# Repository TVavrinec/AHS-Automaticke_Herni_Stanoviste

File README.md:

# AHS-Specifikace hrubý popis
Specifikace AHS (Automatické Herní Stanoviště), nástupcem Lucerny a BlackBoxu
Jde o statické zařízení sloužící jako herní stanoviště.
Mělo by tedy být mobilní jen natolik aby nebyl problém jej přepravovat.
Není ale cílem aby ho hráči nosil během hry nosil s sebou.

# Konkrétní uživatelské požadavky
- Dva LED kruhy jeden radiální a jeden axiální (tak jak na lucerně)
- Tlaková plocha (tak jak na lucerně ale doladit samotnou kontaktní plochu aby se zvýšila spolehlivost)
- Výdrž na baterii alespoň pět hodin aby bylo možné organizovat čtyřhodinovou hru s rezervou na nastavování atd.
- Elegantní zapínání (znamená ne powerbankou a kabelem!!!)
- Snadná montáž (znamená ne 16h na jeden kus)
- Servisně snadné připojený komunikační/GPS modul uvnitř zařízení (A9, MC60 ???)
- Servisně snadné připojená dvířka a jiné moduly vně základního zařízení
- Základní zvuková odezva (pískle, na pokročilejší zvuk bude modul)

# Základní struktura elektroniky

Elektronika je rozdělena na dvě desky, Led dsku a Hlavní desku.

## LedDeska

Oproti předchozím verzím je přidán LED-kruh i na druhou stranu LedDesky abychom se zbavili LED-pásku a odebrat výstupní konektor
- Přední axiální LEDkoví kruh z 60ti RGB LEDek
- Zadní radiální LEDkoví kruh z 60ti RGB LEDek (buď přímo radiální [buce cca třikrát dražší] nebo axiální s odraznou plochou [radializátorem])
- LDC1614 nebo LDC1314 + čtyři snímací cívky pro snímání tlakové plochy

## Hlavní deska 
- ESP32-S3
- Interní systémy
    - dohodnutí PD
    - bzučák (bez oscilátorové)
    - Power manager
        - jednočlánek
        - zapínání (ovládání na Mini UI)
        - step-up na 5V
        - LDO na 3V3
        - LDO na 1V8
        - nabíječka
        - hw ochrana podvybití
- Konektory na
    - ledDesku
    - komunikační modul
    - externí moduly
    - USB-C (nabíjení a primární programování [USB přímo z ESP, nebudeme zabírat místo převodníkem])
    - mini UI
    - kontakty na SemiSemafoří programátor
    - zbylé piny

## Mini UI
Minimalistické vývojové rozhraní.
- RESET tlačítka
- BOOT tlačítka
- zapínací tlačítko
- vypínací tlačítko bych spojil se zapínacím nebo možná s resetem (dlouhí stisk vypíná, nechci tam mít příliž mnoho tlačítek)
- dvě tlačítka 
- dvě obyčejné ledky?

# Popis jednotlivých bodů
## Interní systémy
### Dohodnutí PD
Vykomunykování vyššího napětí a proudu zajišťuje čip **AP33772** připojený na I2C ESP.

### Bzučák
Piezzo připojené mezi dva piny ESP aby bylo možné programově nastavit frekvenci a částečně i hlasitost.

### Power manager
#### Zapínání
Umožňuje uživateli zařízení zapnout tlačítkem.
Vypnutí je možné provést softwarově z ESP.

#### Step-up na 5V
Zajišťuje napájení světelným kruhům a externím modulům.
Maximální proud je sto ukrmit oba světelné kruhy a moduloví konektor.
*Je tedy sto dodat cca 7A*

#### LDO na 3V3
Z napětí 3.3V je napájeno ESP32S3, LCD1x14 a PD sink AP33772.
*Je tedy sto dodat cca 1A*

#### Nabíječka
Nabíjení probíhá přez USB-C, nabíječka je proto schopna rovzu z 5V.
Aby se ale zařízení dalo nabít rychleji je možno použít standard PowerDelivery s napětí až 21V.
Na nabíjení je proto použit chip **BQ24179YBGR**.

### Hw ochrana podvybití
Kvuli ochraně baterie se zařízení vypne pokud se baterie vybije pod 2.8V (podle https://web.archive.org/web/20101122230718/https://www.panasonic.com/industrial/includes/pdf/Panasonic_LiIon_Charging.pdf by napětí na článek nemělo klesnout pod 2.3V a AHS přidává rezervu 0.1V [ https://web.archive.org/web/20100413182032/http://www.panasonic.com/industrial/batteries-oem/oem/lithium-ion.aspx ]) 

## Konektory
### USB-C
D+ D- jsou napojeny přímo na ESP a CC piny jsou napojeny na AP33772(to přes I2C na ESP).

### Konektor komunikačního modulu
Na konektor, je z ESP vyvedeno: 
-   I2C
-   celý UART
-   FUL_CARD_POWER_OFF
-   RESET
-   WoWWAN (interrupt)

a mimo ESP je na konektoru:
-   napájení přímo z baterie
-   SIM

Pin-out M2 konektoru z https://files.waveshare.com/upload/0/02/SIM7600X-M2_Hardware_Design_V1.01.pdf

### Konektor na LedDesku

<-1--13-> 5V

<----14-> LED-DO

<-15-27-> GND

<----28-> 3V3

<----29-> LDC-GND

-----30-> LDC-INT

<----31-> SDA

<----32-- SCL

Pull-upy na I2C a na LDC-INT mají 4.7kΩ.
LDC-GND je na hlavní desce normální GND ale kvůli velkým proudum do ledek je v kabelu a na Led desce vedena odděleně.
Konektorem na 5V proteče alespoň 5A.

### Moduloví konektor

---> USART-RX

<--> 5V

<--> GND

<--- USART-TX

<--> GND

<--> 5V

---> INI

Všechny moduly jsou připojeny na jeden RX pin AHS.
Proto musí firmware AHS zajistit aby dva moduli nevysílali současně!
Každý modul má TX připojen přes rezistor 180Ω jako ochranu.

Interrupt na modulech se chová jako open-collector což je zajistit hardwarově.

AHS zajišťuje odolnost proti rušení na všech vstupních vodičích pomocí 4.7kΩ pull-up a odolnost proti zkratu na datových výstupních vodičích pomocí 180Ω.
Zároveň zajistí ESD ochranu všem vodičům co vedou z/do AHS.

Konektor je zároveň sto dodat napájení 5V s proudem v součty 2A.

Komunikace muže být vedena kabelem o délce až 25cm při komunikační rychlosti 5Mbps.
*Při dalším prodlužování linky bude třeba vodiče RX a TX vlnově přizpůsobit a doplnit linku terminátory*

## mechanická část
Základ AHS je mechanicky krátký válec s tlakovou plochou na horní ploše.
Kolem tlakové plochu je umístěn axiální světelný kruh a v horní části válcové plochy je radiální světelný kruh.

- Tělo minimálně v prototypu tisknuté
- Vyzkoušet různé provedení kontaktní plochy
    - Stejně jako na předchozí verzi FR4 ale tlustší aby se tolik nekroutila
    - PCB s hliníkovým jádrem + zalití do epoxidu nebo jiné dostatečně průsvitné hmoty
- Konektor externích modulu, USB-C a mini UI překrýt krytkou (ochrana před bordelem a náhodným mačkáním na tlačítka)

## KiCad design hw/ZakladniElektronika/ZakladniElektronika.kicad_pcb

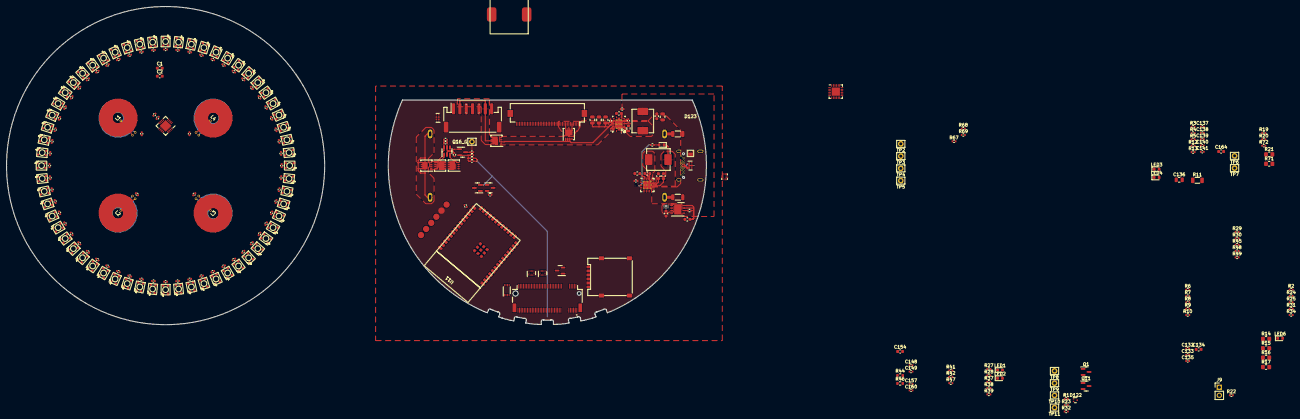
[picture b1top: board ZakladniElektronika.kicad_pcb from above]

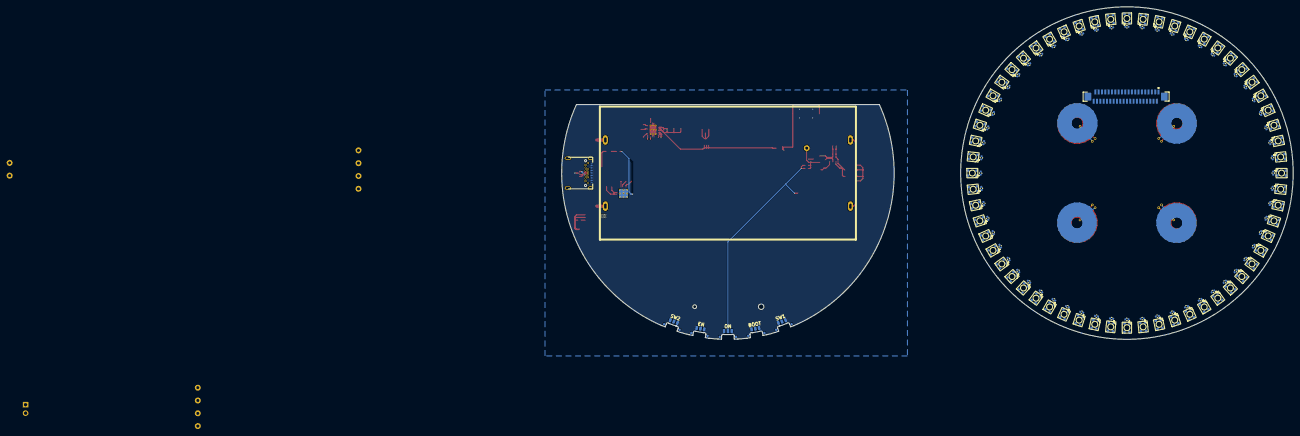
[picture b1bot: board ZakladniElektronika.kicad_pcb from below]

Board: 4 copper layers, 220.0 x 100.0 mm, 405 parts (128 on the bottom side), 258 nets.

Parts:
BZ1: Buzzer; PKLCS1212E-(RH-Logic_piezzo)
C1, C2, C6, C134, C145, C146, C147, C155: 10u; C_0603_1608Metric
C3, C132, C133, C138, C141, C142, C144, C148, C149, C163, C166: 1u; C_0402_1005Metric
C4, C7, C12, C13, C14, C15, C16, C17, C18, C19, C20, C21, C22, C23, C24, C25, C26, C27, C28, C29, C30, C31, C32, C33, C34, C35, C36, C37, C38, C39, C40, C41, C42, C43, C44, C45, C46, C47, C48, C49, C50, C51, C52, C53, C54, C55, C56, C57, C58, C59, C60, C61, C62, C63, C64, C65, C66, C67, C68, C69, C70, C71, C72, C73, C74, C75, C76, C77, C78, C79, C80, C81, C82, C83, C84, C85, C86, C87, C88, C89, C90, C91, C92, C93, C94, C95, C96, C97, C98, C99, C100, C101, C102, C103, C104, C105, C106, C107, C108, C109, C110, C111, C112, C113, C114, C115, C116, C117, C118, C119, C120, C121, C122, C123, C124, C125, C126, C127, C128, C129, C130, C131, C135, C137, C139, C140, C143, C151: 100n; C_0402_1005Metric
C5, C153, C156, C159: 22u; C_0805_2012Metric
C8, C9, C10, C11: 1000p; C_0402_1005Metric
C136: 10u; C_0805_2012Metric
C150, C154, C164: 4.7u; C_0603_1608Metric
C152, C165: 47n; C_0603_1608Metric
C157: 10n; C_0402_1005Metric
C160: 100p; C_0402_1005Metric
D1, D2, D3, D4, D5, D6, D7, D8, D9, D10, D11, D12, D13, D14, D15, D16, D17, D18, D19, D20, D21, D22, D23, D24, D25, D26, D27, D28, D29, D30, D31, D32, D33, D34, D35, D36, D37, D38, D39, D40, D41, D42, D43, D44, D45, D46, D47, D48, D49, D50, D51, D52, D53, D54, D55, D56, D57, D58, D59, D60, D61, D62, D63, D64, D65, D66, D67, D68, D69, D70, D71, D72, D73, D74, D75, D76, D77, D78, D79, D80, D81, D82, D83, D84, D85, D86, D87, D88, D89, D90, D91, D92, D93, D94, D95, D96, D97, D98, D99, D100, D101, D102, D103, D104, D105, D106, D107, D108, D109, D110, D111, D112, D113, D114, D115, D116, D117, D118, D119, D120: WS2812B; 3528RGBW-WS2812B
D122: D_Dual_CommonCathode_AAK_Parallel; SOT-723
D123: PTVSHC3N24; DFN3-2x2
F3, F4: 3A-6A; L_1206_3216Metric
J2: USB_C_Receptacle_USB2.0; USB31-TYPEC-33141-2FS
J3: Conn_2Rows-75Pins; Conn_M2
J4: Conn_01x07; JST_PH_S7B-PH-SM4-TB_1x07-1MP_P2.00mm_Horizontal
J7: ESP-Programing_conector
J9: Conn_01x02; PinHeader_1x02_P2.54mm_Vertical
J10: Conn_01x40; AFC11-S40ICC-00
J11: Conn_01x40; Hirose_FH12-40S-0.5SH_1x40-1MP_P0.50mm_Horizontal
L1, L2, L3, L4: L; PCB_coil
L6: 1.2u; L_Abracon_ASPI-0630LR
L7: 2.2u; L_Abracon_ASPI-0630LR
LED1, LED3, LED4, LED5, LED6: red; LED_0603_1608Metric
LED2: green; LED_0603_1608Metric
Q1, Q11, Q17: Q_NMOS_DGS-L; SOT-23
Q7: Q_PMOS_DGS-L; SOT-23
Q10, Q13: Q_PMOS_DGS-P; Diodes_PowerDI3333-8
Q12, Q14, Q15: Q_NMOS_DGS-P; Diodes_PowerDI3333-8
Qe: Q_NMOS_DGS-L; SOT-23
R1, R6, R7, R8, R9, R10, R12, R19, R20, R22, R23, R32, R34, R67, R70: 10k; R_0402_1005Metric
R2, R26, R41, R50, R60: 200k; R_0402_1005Metric
R3, R4: 5.1k; R_0402_1005Metric
R5, R13, R18, R24, R25, R31, R37, R38, R39, R45, R48: 4.7k; R_0402_1005Metric
R11: 10m; R_1206_3216Metric
R14, R16: 0-nc; R_0805_2012Metric_Pad1.20x1.40mm_HandSolder
R15, R17, R21, R71: 0; R_0805_2012Metric_Pad1.20x1.40mm_HandSolder
R27, R28: 1k; R_0402_1005Metric
R29, R30, R49, R69: 200; R_0402_1005Metric
R33: 2k; R_0402_1005Metric
R35: 470; R_0402_1005Metric
R36, R68: 1M; R_0402_1005Metric
R42: 3.92k; R_0402_1005Metric
R43, R44: 150k; R_0603_1608Metric
R46: 56k; R_0603_1608Metric
R47: 17.4k; R_0402_1005Metric
R72: 100; R_0402_1005Metric
SW1, SW2: SW_Push; TCF2QR
SW3: ON; TCF2QR
SW4: BOOT; TCF2QR
SW5: EN; TCF2QR
TP1: Q16_G; Pin_D0.9mm_L10.0mm_W2.4mm_FlatFork
TP2: TestPoint-BAT; Pin_D0.9mm_L10.0mm_W2.4mm_FlatFork
TP3: TestPoint-VCC; Pin_D0.9mm_L10.0mm_W2.4mm_FlatFork
TP4: TestPoint-BUTTON_ON; Pin_D0.9mm_L10.0mm_W2.4mm_FlatFork
TP5: TestPoint-EN_ALL; Pin_D0.9mm_L10.0mm_W2.4mm_FlatFork
TP6: TestPoint-Charger_QON; Pin_D0.9mm_L10.0mm_W2.4mm_FlatFork
TP7: TestPoint-Charger_ILIM; Pin_D0.9mm_L10.0mm_W2.4mm_FlatFork
TP8: TestPoint-5V_EN; Pin_D0.9mm_L10.0mm_W2.4mm_FlatFork
TP9: TestPoint-5V; Pin_D0.9mm_L10.0mm_W2.4mm_FlatFork
TP10: TestPoint-5V_B; Pin_D0.9mm_L10.0mm_W2.4mm_FlatFork
TP11: TestPoint-5V_A; Pin_D0.9mm_L10.0mm_W2.4mm_FlatFork
U1: LDC1614; WQFN-16-1EP_4x4mm_P0.5mm_EP2.6x2.6mm
U2, U6: TXB0304RUT; Texas_R-PUQFN-N12
U3: TPS61088RHLR; RHL0020A
U4: AP33772; QFN-24-1EP_4x4mm_P0.5mm_EP2.6x2.6mm
U5, U13: TPD4E02B04DQA; USON-10_2.5x1.0mm_P0.5mm
U7: SL8261D-G3JE; SOT-23-6
U8: PCA9306DC; VSSOP-8_2.3x2mm_P0.5mm
U9: BQ25895RTW; Texas_S-PWQFN-N24_EP2.7x2.7mm_ThermalVias
U11: ESP32-S3-WROOM
U12: LD39200; DFN-8-1EP_4x4mm_P0.8mm_EP2.3x3.24mm
U15: TS3USB3031; Texas_X2QFN-12_1.6x1.6mm_P0.4mm
U17: BateriCell_2x; battery_dock
U52: MCP1700x-180xxTT; SOT-23
U53: SMN-305-ARP7

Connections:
/HlavniDeska/3V3: C134.2, C135.2, C149.1, C155.1, J7.1 (VCC), J9.2, J11.36, LED6.2 (A), R2.1, R9.1, R10.1, R23.1, R34.1, R37.1, R38.1, R39.1, R45.2, R48.2, R67.2, R70.2, U2.11 (VCCB), U6.11 (VCCB), U11.2 (3V3), U12.1 (OUT), U12.2 (OUT), U12.3 (ADJ/SENSE), U15.12 (VCC), U52.3 (VI)
/HlavniDeska/5V-OUT: J11.1, J11.2, J11.3, J11.4, J11.5, J11.6, J11.7, J11.8, J11.9, J11.10, J11.11, J11.12, J11.13, Q13.5 (D), TP10.1
/HlavniDeska/C.D+: J2.A6 (D+), J2.B6 (D+), U13.5 (IO4), U15.11 (D+)
/HlavniDeska/C.D-: J2.A7 (D-), J2.B7 (D-), U13.4 (IO3), U15.10 (D-)
/HlavniDeska/ESP32S3/BOOT: C132.1, J7.4 (BOOT), R9.2, SW4.2, U11.27 (IO00-PU)
/HlavniDeska/ESP32S3/EN: C133.1, J7.3 (EN), R10.2, SW5.2, U11.3 (EN)
/HlavniDeska/ESP32S3/IO01: BZ1.2 (+), U11.39 (IO01)
/HlavniDeska/ESP32S3/IO02: R49.2, U5.4 (IO3), U11.38 (IO02)
/HlavniDeska/ESP32S3/IO03-PD: BZ1.1 (-), R8.1, U11.15 (IO03-PD)
/HlavniDeska/ESP32S3/IO07: U6.10 (B1), U11.7 (IO07)
/HlavniDeska/ESP32S3/IO08: J3.6, U11.12 (IO08)
/HlavniDeska/ESP32S3/IO15: J3.1, U11.8 (IO15)
/HlavniDeska/ESP32S3/IO16: J3.75, U11.9 (IO16)
/HlavniDeska/ESP32S3/IO17: J3.69, U11.10 (IO17)
/HlavniDeska/ESP32S3/IO18: J3.21, U11.11 (IO18)
/HlavniDeska/ESP32S3/IO21: R69.2, U11.23 (IO21)
/HlavniDeska/ESP32S3/IO35: Qe.1 (D), R70.1, U11.28 (IO35)
/HlavniDeska/ESP32S3/IO36: SW1.2, U11.29 (IO36)
/HlavniDeska/ESP32S3/IO37: SW2.2, U11.30 (IO37)
/HlavniDeska/ESP32S3/IO38: LED1.2 (A), U11.31 (IO38)
/HlavniDeska/ESP32S3/IO39: LED2.2 (A), U11.32 (IO39)
/HlavniDeska/ESP32S3/IO41: R29.2, U5.1 (IO1), U11.34 (IO41)
/HlavniDeska/ESP32S3/IO42: R30.2, U5.2 (IO2), U11.35 (IO42)
/HlavniDeska/ESP32S3/IO45-PD: D122.1 (K), Q11.2 (G), R7.1, U11.26 (IO45-PD)
/HlavniDeska/ESP32S3/IO46-PD: D122.2 (K), Q1.2 (G), R6.1, U11.16 (IO46-PD)
/HlavniDeska/ESP32S3/RX_ESP: J7.5 (RX), U11.36 (IO44-RX)
/HlavniDeska/ESP32S3/TX_ESP: J7.6 (TX), U11.37 (IO43-TX)
/HlavniDeska/ESP.D+: U11.14 (IO20-D+), U15.5 (USB2+)
/HlavniDeska/ESP.D-: U11.13 (IO19-D-), U15.6 (USB2-)
/HlavniDeska/GPSKomunikacniModul/1V8: C148.1, R24.1, R25.1, U2.1 (VCCA), U2.12 (OE), U6.1 (VCCA), U6.12 (OE), U8.2 (VREF1), U52.2 (VO)
/HlavniDeska/GPSKomunikacniModul/SCL(1.8V): J3.40, R24.2, U8.3 (SCL1)
/HlavniDeska/GPSKomunikacniModul/SDA(1.8V): J3.42, R25.2, U8.4 (SDA1)
/HlavniDeska/GPSKomunikacniModul/SIM_CD: J3.66, U53.D (CD)
/HlavniDeska/GPSKomunikacniModul/SIM_CLK: J3.32, U53.3 (CLK)
/HlavniDeska/GPSKomunikacniModul/SIM_I/O: J3.34, U53.7 (I/O)
/HlavniDeska/GPSKomunikacniModul/SIM_RST: J3.30, U53.2 (RST)
/HlavniDeska/GPSKomunikacniModul/SIM_VCC: J3.36, U53.1 (VCC)
/HlavniDeska/GPSKomunikacniModul/UART_CTS(O)(1.8V): J3.56, U2.4 (A3)
/HlavniDeska/GPSKomunikacniModul/UART_DTR(I)(1.8V): J3.52, U6.3 (A2)
/HlavniDeska/GPSKomunikacniModul/UART_RTS(I)(1.8V): J3.54, U2.5 (A4)
/HlavniDeska/GPSKomunikacniModul/UART_RXD(I)(1.8V): R14.1, R15.1, U2.3 (A2)
/HlavniDeska/GPSKomunikacniModul/UART_TXD(O)(1.8V): R16.1, R17.1, U2.2 (A1)
/HlavniDeska/INT: J3.23, J11.38, R34.2, R38.2, U4.9 (GPIO3), U9.7 (INT), U11.4 (IO04)
/HlavniDeska/IO40: J11.27, U11.33 (IO40)
/HlavniDeska/KM_CST: U2.8 (B3), U11.19 (IO11)
/HlavniDeska/KM_DTR: U6.9 (B2), U11.17 (IO09)
/HlavniDeska/KM_RTS: U2.7 (B4), U11.18 (IO10)
/HlavniDeska/KM_RXD: U2.9 (B2), U11.20 (IO12)
/HlavniDeska/KM_TXD: U2.10 (B1), U11.21 (IO13)
/HlavniDeska/KomunikacniModul.D+: J3.9, U15.7 (MHL+)
/HlavniDeska/KomunikacniModul.D-: J3.7, U15.8 (MHL-)
/HlavniDeska/ModulovyKonektor/5V: J4.2, J4.6, Q10.5 (D), TP11.1, U5.5 (IO4)
/HlavniDeska/Nabijecka.D+: U9.2 (D+), U15.3 (USB1+)
/HlavniDeska/Nabijecka.D-: U9.3 (D-), U15.4 (USB1-)
/HlavniDeska/SCL: J11.40, R37.2, U4.5 (SCL), U8.6 (SCL2), U9.5 (SCL), U11.5 (IO05)
/HlavniDeska/SDA: J11.39, R39.2, U4.4 (SDA), U8.5 (SDA2), U9.6 (SDA), U11.6 (IO06)
/HlavniDeska/SpravceNapajeni/5V-IN: C142.1, C153.1, C156.1, C159.1, Q10.1 (S), Q10.2 (S), Q10.3 (S), Q13.1 (S), Q13.2 (S), Q13.3 (S), R1.1, R32.1, R46.1, TP9.1, U3.14 (VOUT), U3.15 (VOUT), U3.16 (VOUT)
/HlavniDeska/SpravceNapajeni/DSEL: R23.2, U9.24 (DSEL), U15.1 (SEL0)
/HlavniDeska/SpravceNapajeni/Nabijecka/STAT: R18.1, U9.4 (STAT)
/HlavniDeska/SpravceNapajeni/NapajeciRozcesti/EN-5V: D122.3 (A), R41.2, TP8.1, U3.2 (EN)
/HlavniDeska/SpravceNapajeni/VBUS: C137.2, C141.1, C166.1, R11.2, U4.22 (VUSB), U4.24 (VCC), U9.1 (VBUS)
/HlavniDeska/USB/AP-3V3: C139.2, U4.12 (3V3)
/HlavniDeska/USB/USB_CC1: J2.A5 (CC1), R4.1, U4.17 (CC1), U13.1 (IO1)
/HlavniDeska/USB/USB_CC2: J2.B5 (CC2), R3.1, U4.16 (CC2), U13.2 (IO2)
/HlavniDeska/USB/V_USB: C136.1, C137.1, D123.3 (K), J2.A4 (VBUS), J2.A9 (VBUS), J2.B4 (VBUS), J2.B9 (VBUS), LED3.2 (A), R11.1, U4.1 (ISENP)
/LedDeska/3V3: C3.1, C4.1, J10.36, U1.7 (VDD)
/LedDeska/5V: C1.1, C2.1, C12.1, C13.1, C14.1, C15.1, C16.1, C17.1, C18.1, C19.1, C20.1, C21.1, C22.1, C23.1, C24.1, C25.1, C26.1, C27.1, C28.1, C29.1, C30.1, C31.1, C32.1, C33.1, C34.1, C35.1, C36.1, C37.1, C38.1, C39.1, C40.1, C41.1, C42.1, C43.1, C44.1, C45.1, C46.1, C47.1, C48.1, C49.1, C50.1, C51.1, C52.1, C53.1, C54.1, C55.1, C56.1, C57.1, C58.1, C59.1, C60.1, C61.1, C62.1, C63.1, C64.1, C65.1, C66.1, C67.1, C68.1, C69.1, C70.1, C71.1, C72.1, C73.1, C74.1, C75.1, C76.1, C77.1, C78.1, C79.1, C80.1, C81.1, C82.1, C83.1, C84.1, C85.1, C86.1, C87.1, C88.1, C89.1, C90.1, C91.1, C92.1, C93.1, C94.1, C95.1, C96.1, C97.1, C98.1, C99.1, C100.1, C101.1, C102.1, C103.1, C104.1, C105.1, C106.1, C107.1, C108.1, C109.1, C110.1, C111.1, C112.1, C113.1, C114.1, C115.1, C116.1, C117.1, C118.1, C119.1, C120.1, C121.1, C122.1, C123.1, C124.1, C125.1, C126.1, C127.1, C128.1, C129.1, C130.1, C131.1, D1.1 (VDD), D2.1 (VDD), D3.1 (VDD), D4.1 (VDD), D5.1 (VDD), D6.1 (VDD), D7.1 (VDD), D8.1 (VDD), D9.1 (VDD), D10.1 (VDD), D11.1 (VDD), D12.1 (VDD), D13.1 (VDD), D14.1 (VDD), D15.1 (VDD), D16.1 (VDD), D17.1 (VDD), D18.1 (VDD), D19.1 (VDD), D20.1 (VDD), D21.1 (VDD), D22.1 (VDD), D23.1 (VDD), D24.1 (VDD), D25.1 (VDD), D26.1 (VDD), D27.1 (VDD), D28.1 (VDD), D29.1 (VDD), D30.1 (VDD), D31.1 (VDD), D32.1 (VDD), D33.1 (VDD), D34.1 (VDD), D35.1 (VDD), D36.1 (VDD), D37.1 (VDD), D38.1 (VDD), D39.1 (VDD), D40.1 (VDD), D41.1 (VDD), D42.1 (VDD), D43.1 (VDD), D44.1 (VDD), D45.1 (VDD), D46.1 (VDD), D47.1 (VDD), D48.1 (VDD), D49.1 (VDD), D50.1 (VDD), D51.1 (VDD), D52.1 (VDD), D53.1 (VDD), D54.1 (VDD), D55.1 (VDD), D56.1 (VDD), D57.1 (VDD), D58.1 (VDD), D59.1 (VDD), D60.1 (VDD), D61.1 (VDD), D62.1 (VDD), D63.1 (VDD), D64.1 (VDD), D65.1 (VDD), D66.1 (VDD), D67.1 (VDD), D68.1 (VDD), D69.1 (VDD), D70.1 (VDD), D71.1 (VDD), D72.1 (VDD), D73.1 (VDD), D74.1 (VDD), D75.1 (VDD), D76.1 (VDD), D77.1 (VDD), D78.1 (VDD), D79.1 (VDD), D80.1 (VDD), D81.1 (VDD), D82.1 (VDD), D83.1 (VDD), D84.1 (VDD), D85.1 (VDD), D86.1 (VDD), D87.1 (VDD), D88.1 (VDD), D89.1 (VDD), D90.1 (VDD), D91.1 (VDD), D92.1 (VDD), D93.1 (VDD), D94.1 (VDD), D95.1 (VDD), D96.1 (VDD), D97.1 (VDD), D98.1 (VDD), D99.1 (VDD), D100.1 (VDD), D101.1 (VDD), D102.1 (VDD), D103.1 (VDD), D104.1 (VDD), D105.1 (VDD), D106.1 (VDD), D107.1 (VDD), D108.1 (VDD), D109.1 (VDD), D110.1 (VDD), D111.1 (VDD), D112.1 (VDD), D113.1 (VDD), D114.1 (VDD), D115.1 (VDD), D116.1 (VDD), D117.1 (VDD), D118.1 (VDD), D119.1 (VDD), D120.1 (VDD), J10.1, J10.2, J10.3, J10.4, J10.5, J10.6, J10.7, J10.8, J10.9, J10.10, J10.11, J10.12, J10.13
/LedDeska/AN-GND: C3.2, C4.2, J10.37, U1.3 (CLKIN), U1.4 (ADDR), U1.6 (SD), U1.8 (GND), U1.17 (GND)
/LedDeska/INT-LDC: J10.38, U1.5 (INTB)
/LedDeska/LED-GND: C1.2, C2.2, C12.2, C13.2, C14.2, C15.2, C16.2, C17.2, C18.2, C19.2, C20.2, C21.2, C22.2, C23.2, C24.2, C25.2, C26.2, C27.2, C28.2, C29.2, C30.2, C31.2, C32.2, C33.2, C34.2, C35.2, C36.2, C37.2, C38.2, C39.2, C40.2, C41.2, C42.2, C43.2, C44.2, C45.2, C46.2, C47.2, C48.2, C49.2, C50.2, C51.2, C52.2, C53.2, C54.2, C55.2, C56.2, C57.2, C58.2, C59.2, C60.2, C61.2, C62.2, C63.2, C64.2, C65.2, C66.2, C67.2, C68.2, C69.2, C70.2, C71.2, C72.2, C73.2, C74.2, C75.2, C76.2, C77.2, C78.2, C79.2, C80.2, C81.2, C82.2, C83.2, C84.2, C85.2, C86.2, C87.2, C88.2, C89.2, C90.2, C91.2, C92.2, C93.2, C94.2, C95.2, C96.2, C97.2, C98.2, C99.2, C100.2, C101.2, C102.2, C103.2, C104.2, C105.2, C106.2, C107.2, C108.2, C109.2, C110.2, C111.2, C112.2, C113.2, C114.2, C115.2, C116.2, C117.2, C118.2, C119.2, C120.2, C121.2, C122.2, C123.2, C124.2, C125.2, C126.2, C127.2, C128.2, C129.2, C130.2, C131.2, D1.3 (VSS), D2.3 (VSS), D3.3 (VSS), D4.3 (VSS), D5.3 (VSS), D6.3 (VSS), D7.3 (VSS), D8.3 (VSS), D9.3 (VSS), D10.3 (VSS), D11.3 (VSS), D12.3 (VSS), D13.3 (VSS), D14.3 (VSS), D15.3 (VSS), D16.3 (VSS), D17.3 (VSS), D18.3 (VSS), D19.3 (VSS), D20.3 (VSS), D21.3 (VSS), D22.3 (VSS), D23.3 (VSS), D24.3 (VSS), D25.3 (VSS), D26.3 (VSS), D27.3 (VSS), D28.3 (VSS), D29.3 (VSS), D30.3 (VSS), D31.3 (VSS), D32.3 (VSS), D33.3 (VSS), D34.3 (VSS), D35.3 (VSS), D36.3 (VSS), D37.3 (VSS), D38.3 (VSS), D39.3 (VSS), D40.3 (VSS), D41.3 (VSS), D42.3 (VSS), D43.3 (VSS), D44.3 (VSS), D45.3 (VSS), D46.3 (VSS), D47.3 (VSS), D48.3 (VSS), D49.3 (VSS), D50.3 (VSS), D51.3 (VSS), D52.3 (VSS), D53.3 (VSS), D54.3 (VSS), D55.3 (VSS), D56.3 (VSS), D57.3 (VSS), D58.3 (VSS), D59.3 (VSS), D60.3 (VSS), D61.3 (VSS), D62.3 (VSS), D63.3 (VSS), D64.3 (VSS), D65.3 (VSS), D66.3 (VSS), D67.3 (VSS), D68.3 (VSS), D69.3 (VSS), D70.3 (VSS), D71.3 (VSS), D72.3 (VSS), D73.3 (VSS), D74.3 (VSS), D75.3 (VSS), D76.3 (VSS), D77.3 (VSS), D78.3 (VSS), D79.3 (VSS), D80.3 (VSS), D81.3 (VSS), D82.3 (VSS), D83.3 (VSS), D84.3 (VSS), D85.3 (VSS), D86.3 (VSS), D87.3 (VSS), D88.3 (VSS), D89.3 (VSS), D90.3 (VSS), D91.3 (VSS), D92.3 (VSS), D93.3 (VSS), D94.3 (VSS), D95.3 (VSS), D96.3 (VSS), D97.3 (VSS), D98.3 (VSS), D99.3 (VSS), D100.3 (VSS), D101.3 (VSS), D102.3 (VSS), D103.3 (VSS), D104.3 (VSS), D105.3 (VSS), D106.3 (VSS), D107.3 (VSS), D108.3 (VSS), D109.3 (VSS), D110.3 (VSS), D111.3 (VSS), D112.3 (VSS), D113.3 (VSS), D114.3 (VSS), D115.3 (VSS), D116.3 (VSS), D117.3 (VSS), D118.3 (VSS), D119.3 (VSS), D120.3 (VSS), J10.14, J10.15, J10.16, J10.17, J10.18, J10.19, J10.20, J10.21, J10.22, J10.23, J10.24, J10.25, J10.26
/LedDeska/LedRing-Axial/DOUT: D60.2 (DOUT), D61.4 (DIN)
/LedDeska/SCL: J10.40, U1.1 (SCL)
/LedDeska/SDA: J10.39, U1.2 (SDA)
/LedDeska/WS2812: D1.4 (DIN), J10.27
GND: C5.2, C6.2, C7.2, C132.2, C133.2, C134.1, C135.1, C136.2, C138.2, C139.1, C140.1, C141.2, C142.2, C145.2, C146.2, C147.2, C148.2, C149.2, C150.2, C152.2, C153.2, C154.2, C155.2, C156.2, C157.2, C159.2, C160.2, C163.2, C164.2, C166.2, D123.1 (A), D123.2 (A), J2.A1 (GND), J2.A12 (GND), J2.B1 (GND), J2.B12 (GND), J2.S1 (SHIELD), J3.3, J3.5, J3.11, J3.25, J3.27, J3.33, J3.39, J3.45, J3.51, J3.57, J3.71, J3.73, J4.3, J4.5, J7.2 (GND), J11.14, J11.15, J11.16, J11.17, J11.18, J11.19, J11.20, J11.21, J11.22, J11.23, J11.24, J11.25, J11.26, J11.37, Q1.3 (S), Q11.3 (S), Q14.1 (S), Q14.2 (S), Q14.3 (S), Q17.3 (S), Qe.3 (S), R3.2, R4.2, R5.1, R6.2, R7.2, R8.2, R12.1, R13.1, R19.2, R21.1, R22.2, R27.1, R28.1, R33.1, R41.1, R44.2, R47.1, R68.1, R71.1, R72.2, SW1.1, SW2.1, SW3.1, SW4.1, SW5.1, U2.6 (GND), U3.0 (PGND), U3.20 (AGND), U3.21 (PGND), U4.3 (GND), U4.25 (GND), U5.3 (G), U5.8 (G), U6.6 (GND), U8.1 (GND), U9.17 (PGND), U9.18 (PGND), U9.25 (PGND), U11.1 (GND), U11.40 (GND), U11.41 (GND), U12.4 (GND), U12.9 (GND), U13.3 (G), U13.8 (G), U15.9 (GND), U52.1 (GND), U53.5 (GND)
unnamed: C157.1, R42.2
unnamed: C165.1, L7.1, U9.19 (SW), U9.20 (SW)
unnamed: D1.2 (DOUT), D7.4 (DIN)
unnamed: D2.4 (DIN), D55.2 (DOUT)
unnamed: D2.2 (DOUT), D8.4 (DIN)
unnamed: D3.4 (DIN), D56.2 (DOUT)
unnamed: D3.2 (DOUT), D9.4 (DIN)
unnamed: D4.4 (DIN), D57.2 (DOUT)
unnamed: D5.4 (DIN), D58.2 (DOUT)
unnamed: D4.2 (DOUT), D10.4 (DIN)
unnamed: D10.2 (DOUT), D16.4 (DIN)
unnamed: D5.2 (DOUT), D11.4 (DIN)
unnamed: D11.2 (DOUT), D17.4 (DIN)
unnamed: D6.2 (DOUT), D12.4 (DIN)
unnamed: D12.2 (DOUT), D18.4 (DIN)
unnamed: D7.2 (DOUT), D13.4 (DIN)
unnamed: D13.2 (DOUT), D19.4 (DIN)
unnamed: D8.2 (DOUT), D14.4 (DIN)
unnamed: D14.2 (DOUT), D20.4 (DIN)
unnamed: D9.2 (DOUT), D15.4 (DIN)
unnamed: D15.2 (DOUT), D21.4 (DIN)
unnamed: D16.2 (DOUT), D22.4 (DIN)
unnamed: D17.2 (DOUT), D23.4 (DIN)
unnamed: D18.2 (DOUT), D24.4 (DIN)
unnamed: D19.2 (DOUT), D25.4 (DIN)
unnamed: D20.2 (DOUT), D26.4 (DIN)
unnamed: D21.2 (DOUT), D27.4 (DIN)
unnamed: D22.2 (DOUT), D28.4 (DIN)
unnamed: D23.2 (DOUT), D29.4 (DIN)
unnamed: D24.2 (DOUT), D30.4 (DIN)
unnamed: D25.2 (DOUT), D31.4 (DIN)
unnamed: D26.2 (DOUT), D32.4 (DIN)
unnamed: D27.2 (DOUT), D33.4 (DIN)
unnamed: D28.2 (DOUT), D34.4 (DIN)
unnamed: D29.2 (DOUT), D35.4 (DIN)
unnamed: D30.2 (DOUT), D36.4 (DIN)
unnamed: D31.2 (DOUT), D37.4 (DIN)
unnamed: D32.2 (DOUT), D38.4 (DIN)
unnamed: D33.2 (DOUT), D39.4 (DIN)
unnamed: D34.2 (DOUT), D40.4 (DIN)
unnamed: D35.2 (DOUT), D41.4 (DIN)
unnamed: D36.2 (DOUT), D42.4 (DIN)
unnamed: D37.2 (DOUT), D43.4 (DIN)
unnamed: D38.2 (DOUT), D44.4 (DIN)
unnamed: D39.2 (DOUT), D45.4 (DIN)
unnamed: D40.2 (DOUT), D46.4 (DIN)
unnamed: D41.2 (DOUT), D47.4 (DIN)
unnamed: D42.2 (DOUT), D48.4 (DIN)
unnamed: D43.2 (DOUT), D49.4 (DIN)
unnamed: D44.2 (DOUT), D50.4 (DIN)
unnamed: D45.2 (DOUT), D51.4 (DIN)
unnamed: D46.2 (DOUT), D52.4 (DIN)
unnamed: D47.2 (DOUT), D53.4 (DIN)
unnamed: D48.2 (DOUT), D54.4 (DIN)
unnamed: D49.2 (DOUT), D55.4 (DIN)
unnamed: D50.2 (DOUT), D56.4 (DIN)
unnamed: D51.2 (DOUT), D57.4 (DIN)
unnamed: D52.2 (DOUT), D58.4 (DIN)
unnamed: D53.2 (DOUT), D59.4 (DIN)
unnamed: D54.2 (DOUT), D60.4 (DIN)
unnamed: D6.4 (DIN), D59.2 (DOUT)
unnamed: D61.2 (DOUT), D67.4 (DIN)
unnamed: D62.2 (DOUT), D68.4 (DIN)
unnamed: D63.2 (DOUT), D69.4 (DIN)
unnamed: D64.2 (DOUT), D70.4 (DIN)
unnamed: D65.2 (DOUT), D71.4 (DIN)
unnamed: D66.2 (DOUT), D72.4 (DIN)
unnamed: D67.2 (DOUT), D73.4 (DIN)
unnamed: D68.2 (DOUT), D74.4 (DIN)
unnamed: D69.2 (DOUT), D75.4 (DIN)
unnamed: D70.2 (DOUT), D76.4 (DIN)
unnamed: D71.2 (DOUT), D77.4 (DIN)
unnamed: D72.2 (DOUT), D78.4 (DIN)
unnamed: D73.2 (DOUT), D79.4 (DIN)
unnamed: D74.2 (DOUT), D80.4 (DIN)
unnamed: D75.2 (DOUT), D81.4 (DIN)
unnamed: D76.2 (DOUT), D82.4 (DIN)
unnamed: D77.2 (DOUT), D83.4 (DIN)
unnamed: D78.2 (DOUT), D84.4 (DIN)
unnamed: D79.2 (DOUT), D85.4 (DIN)
unnamed: D80.2 (DOUT), D86.4 (DIN)
unnamed: D81.2 (DOUT), D87.4 (DIN)
unnamed: D82.2 (DOUT), D88.4 (DIN)
unnamed: D83.2 (DOUT), D89.4 (DIN)
unnamed: D84.2 (DOUT), D90.4 (DIN)
unnamed: D85.2 (DOUT), D91.4 (DIN)
unnamed: D86.2 (DOUT), D92.4 (DIN)
unnamed: D87.2 (DOUT), D93.4 (DIN)
unnamed: D88.2 (DOUT), D94.4 (DIN)
unnamed: D89.2 (DOUT), D95.4 (DIN)
unnamed: D90.2 (DOUT), D96.4 (DIN)
unnamed: D91.2 (DOUT), D97.4 (DIN)
unnamed: D92.2 (DOUT), D98.4 (DIN)
unnamed: D93.2 (DOUT), D99.4 (DIN)
unnamed: D94.2 (DOUT), D100.4 (DIN)
unnamed: D100.2 (DOUT), D106.4 (DIN)
unnamed: D95.2 (DOUT), D101.4 (DIN)
unnamed: D101.2 (DOUT), D107.4 (DIN)
unnamed: D96.2 (DOUT), D102.4 (DIN)
unnamed: D102.2 (DOUT), D108.4 (DIN)
unnamed: D97.2 (DOUT), D103.4 (DIN)
unnamed: D103.2 (DOUT), D109.4 (DIN)
unnamed: D98.2 (DOUT), D104.4 (DIN)
unnamed: D104.2 (DOUT), D110.4 (DIN)
unnamed: D99.2 (DOUT), D105.4 (DIN)
unnamed: D105.2 (DOUT), D111.4 (DIN)
unnamed: D106.2 (DOUT), D112.4 (DIN)
unnamed: D107.2 (DOUT), D113.4 (DIN)
unnamed: D108.2 (DOUT), D114.4 (DIN)
unnamed: D109.2 (DOUT), D115.4 (DIN)
unnamed: D110.2 (DOUT), D116.4 (DIN)
unnamed: D111.2 (DOUT), D117.4 (DIN)
unnamed: D112.2 (DOUT), D118.4 (DIN)
unnamed: D113.2 (DOUT), D119.4 (DIN)
unnamed: D114.2 (DOUT), D120.4 (DIN)
unnamed: D62.4 (DIN), D115.2 (DOUT)
unnamed: D63.4 (DIN), D116.2 (DOUT)
unnamed: D64.4 (DIN), D117.2 (DOUT)
unnamed: D65.4 (DIN), D118.2 (DOUT)
unnamed: D66.4 (DIN), D119.2 (DOUT)
unnamed: F3.2, U17.1 (+)
unnamed: F4.2, U17.3 (+)
unnamed: J3.10, R31.1
unnamed: J3.58, R14.2
unnamed: J3.60, R16.2
unnamed: J3.62, R15.2
unnamed: J3.64, R17.2
unnamed: J3.67, U6.2 (A1)
unnamed: J4.1, R29.1, R48.1
unnamed: J4.4, R30.1
unnamed: J4.7, R45.1, R49.1
unnamed: J9.1, R22.1, U15.2 (SEL1)
unnamed: LED1.1 (K), R27.2
unnamed: LED2.1 (K), R28.2
unnamed: LED3.1 (K), R5.2
unnamed: LED4.2 (A), U4.6 (GPIO4)
unnamed: LED4.1 (K), R13.2
unnamed: LED5.2 (A), R18.2
unnamed: C145.1, C146.1, L7.2, LED5.1 (K), U9.15 (SYS), U9.16 (SYS)
unnamed: LED6.1 (K), R31.2
unnamed: Q1.1 (D), Q10.4 (G), R1.2
unnamed: C143.1, Q7.1 (D), R36.2, U7.5 (VCC)
unnamed: Q7.3 (S), R35.2
unnamed: Q11.1 (D), Q13.4 (G), R32.2
unnamed: Q12.5 (D), U17.2 (-), U17.4 (-)
unnamed: Q14.5 (D), Q15.5 (D)
unnamed: Q14.4 (G), U7.3 (OC)
unnamed: Q15.4 (G), U7.1 (OD)
unnamed: C144.1, Q7.2 (G), Q17.1 (D), R26.1, R60.1, TP1.1
unnamed: C163.1, Q17.2 (G), R67.1, R68.2, R69.1, TP5.1
unnamed: C144.2, Qe.2 (G), R26.2, SW3.2, TP4.1
unnamed: C8.1, L1.2, U1.9 (IN0A)
unnamed: C8.2, L1.1, U1.10 (IN0B)
unnamed: C9.1, L2.2, U1.11 (IN1A)
unnamed: C9.2, L2.1, U1.12 (IN1B)
unnamed: C10.1, L3.2, U1.13 (IN2A)
unnamed: C10.2, L3.1, U1.14 (IN2B)
unnamed: C11.1, L4.2, U1.15 (IN3A)
unnamed: C11.2, L4.1, U1.16 (IN3B)
unnamed: C151.2, U3.8 (BOOT)
unnamed: C160.1, R42.1, U3.18 (COMP)
unnamed: R46.2, R47.2, U3.17 (FB)
unnamed: R43.2, U3.3 (FSW)
unnamed: R44.1, U3.19 (ILIM)
unnamed: C152.1, U3.10 (SS)
unnamed: C154.1, U3.1 (VCC)
unnamed: C138.1, U4.20 (5V)
unnamed: C140.2, U4.15 (IFB)
unnamed: R12.2, U4.13 (OTP)
unnamed: C143.2, Q12.1 (S), Q12.2 (S), Q12.3 (S), Q15.1 (S), Q15.2 (S), Q15.3 (S), R36.1, U7.6 (GND)
unnamed: R33.2, U7.2 (VM)
unnamed: R2.2, U8.7 (VREF2), U8.8 (EN)
unnamed: C165.2, U9.21 (BTST)
unnamed: R72.1, TP7.1, U9.10 (ILIM)
unnamed: R21.2, U9.8 (OTG)
unnamed: C147.1, U9.23 (PMID)
unnamed: C164.1, R20.2, U9.22 (REGN)
unnamed: R19.1, R20.1, U9.11 (TS)
unnamed: R71.2, U9.9 (~CE)
unnamed: TP6.1, U9.12 (~QON)
unnamed: R50.2, U12.6 (EN)
SW: C151.1, L6.2, R43.1, U3.4 (SW), U3.5 (SW), U3.6 (SW), U3.7 (SW)
VCC: C5.1, C6.1, C7.1, C150.1, F3.1, F4.1, J3.2, J3.4, J3.70, J3.72, J3.74, L6.1, Q12.4 (G), R35.1, R50.1, R60.2, TP2.1, TP3.1, U3.9 (VIN), U9.13 (BAT), U9.14 (BAT), U12.7 (VCC), U12.8 (VCC)

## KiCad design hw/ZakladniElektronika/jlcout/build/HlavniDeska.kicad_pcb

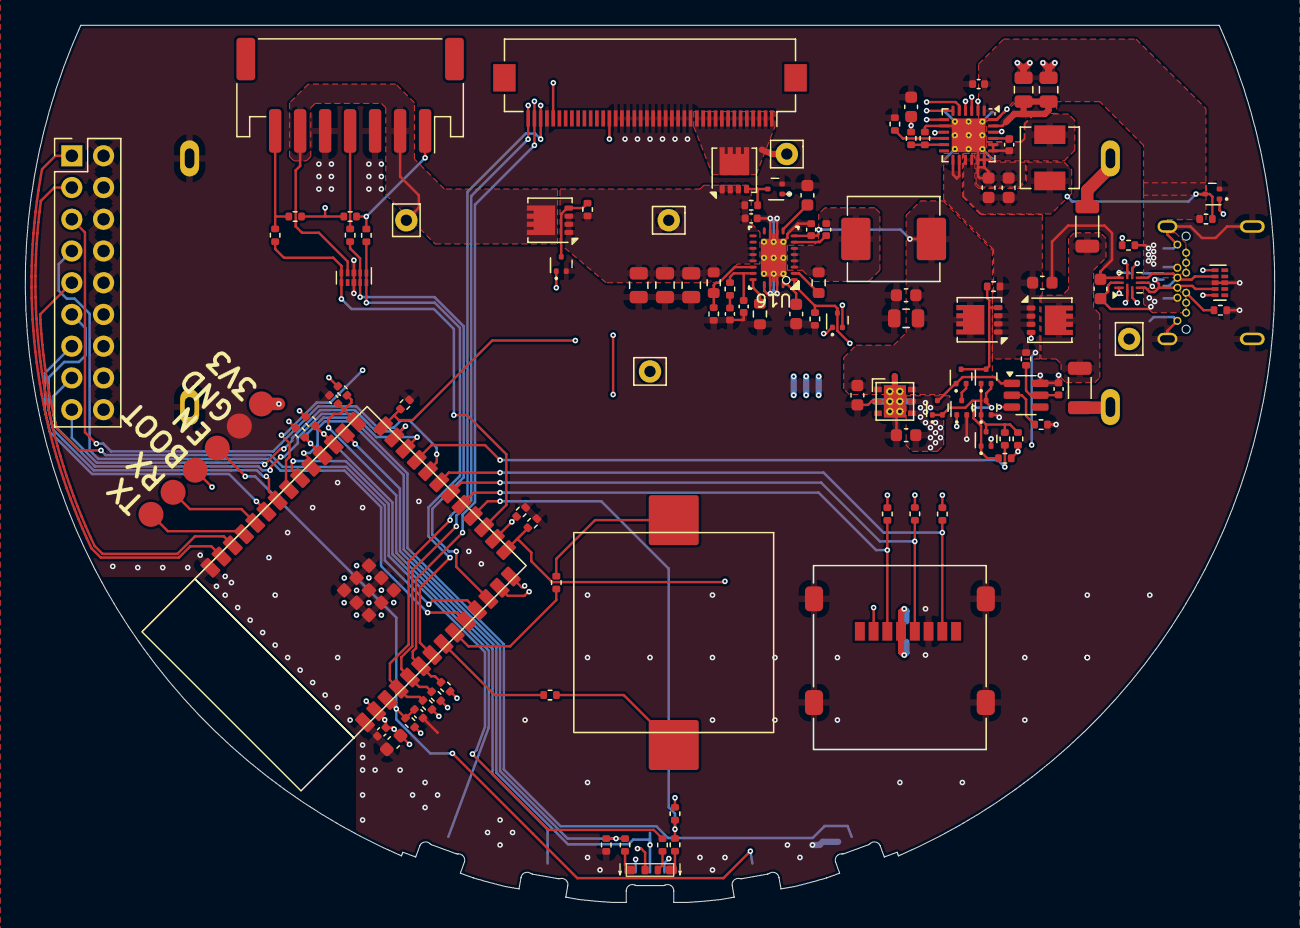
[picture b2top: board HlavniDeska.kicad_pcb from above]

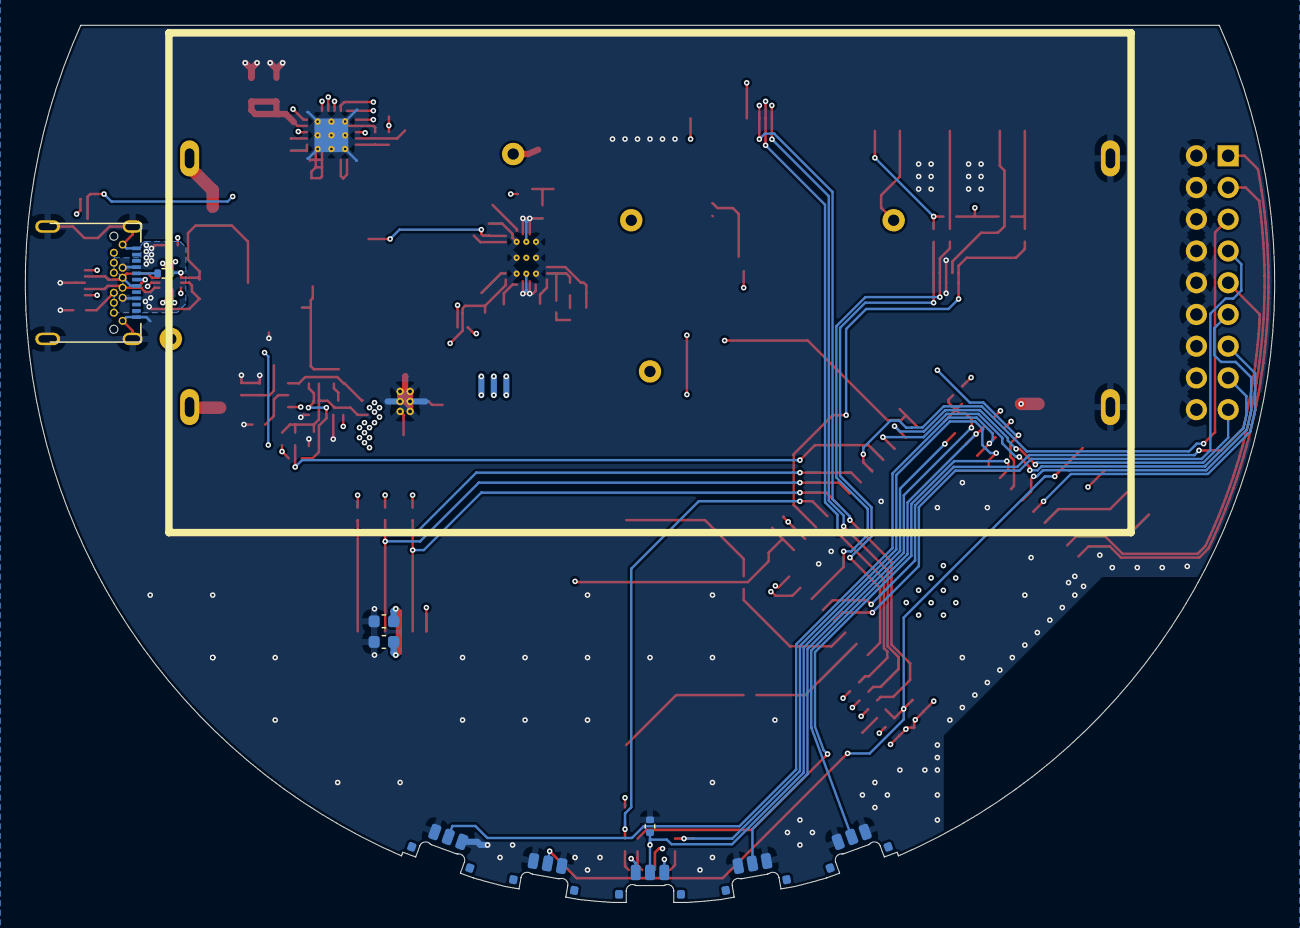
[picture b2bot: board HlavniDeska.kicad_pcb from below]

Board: 4 copper layers, 100.0 x 70.2 mm, 123 parts (11 on the bottom side), 92 nets.

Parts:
B1: HlavniDeska; Board
BZ1: Buzzer; ELKS-PIEZO
C5, C132, C133, C149: 1u; C_0402_1005Metric
C6: 47n; C_0402_1005Metric
C7, C145, C155: 4.7u; C_0603_1608Metric
C134, C143, C152, C159, C160, C161, C162: 10u; C_0603_1608Metric
C135, C144, C146, C148: 100n; C_0402_1005Metric
C136, C137: 10uF; C_0603_1608Metric
C142, C147, C151, C153, C154, C156: 22u; C_0805_2012Metric
C150: 47n; C_0603_1608Metric
C157: 10n; C_0402_1005Metric
C158: 100p; C_0402_1005Metric
D122: D_Dual_CommonCathode_AAK_Parallel; SOT-723
D125: LED_ARGB; XL-3806RGBC-4L
F1, F2: 3A-6A; L_1206_3216Metric
J1: Conn_02x09_Counter_Clockwise; PinHeader_2x09_P2.54mm_Vertical
J2: USB_C_Receptacle_USB2.0; USB31-TYPEC-33141-2FS
J4: Conn_01x07; JST_PH_S7B-PH-SM4-TB_1x07-1MP_P2.00mm_Horizontal
J5: Micro_SD_Card; microSD_HC_Molex_47219-2001
J7: ESP-Programing_conector
J11: Conn_01x40; Hirose_FH12-40S-0.5SH_1x40-1MP_P0.50mm_Horizontal
L5: 1.2u; L_Abracon_ASPI-0630LR
L6: 0.47u; L_Sunlord_MWSA0402S
Q1, Q2, Q4, Q5, Q6, Q7, Q8, Q9, Q28: NMOS; SOT-723
R1, R2, R6, R7, R8, R9, R10, R12, R13, R16, R17, R32, R35, R36, R41, R51, R79: 10k; R_0402_1005Metric
R3, R4: 5.1k; R_0402_1005Metric
R5, R11, R28: 1k; R_0402_1005Metric
R14, R15: 330; R_0402_1005Metric
R19: 150; R_0402_1005Metric
R20: 56k; R_0402_1005Metric
R21, R40: 100k; R_0402_1005Metric
R26: 470; R_0402_1005Metric
R29, R30, R49, R52: 200; R_0402_1005Metric
R34: 2k; R_0402_1005Metric
R37, R38, R39, R45, R48: 4.7k; R_0402_1005Metric
R47, R53: 200k; R_0402_1005Metric
R50, R58: 17.4k; R_0402_1005Metric
R54, R55: 150k; R_0603_1608Metric
R56: 3.92k; R_0402_1005Metric
R57: 56k; R_0603_1608Metric
SW1, SW2: SW_Push; TCF2QR
SW3: ON; TCF2QR
SW4: BOOT; TCF2QR
SW5: EN; TCF2QR
TP1, TP11: TestPoint-5V_A; Pin_D0.9mm_L10.0mm_W2.4mm_FlatFork
TP8: TestPoint-5V_EN; Pin_D0.9mm_L10.0mm_W2.4mm_FlatFork
TP9: TestPoint-5V; Pin_D0.9mm_L10.0mm_W2.4mm_FlatFork
TP10: TestPoint-5V_B; Pin_D0.9mm_L10.0mm_W2.4mm_FlatFork
U2: BL1530TQFN; UQFN-10_1.4x1.8mm_P0.4mm
U3: BQ25895M; Texas_RTW_WQFN-24-1EP_4x4mm_P0.5mm_EP2.7x2.7mm_ThermalVias
U5, U13: TPD4E02B04DQA; USON-10_2.5x1.0mm_P0.5mm
U7, U8, U9, U15: WSD20L75DN33; Diodes_PowerDI3333-8
U10: NCP708; UDFN6-3x3mm
U11: ESP32-S3-WROOM
U12: SL8261D-G3JE; SOT-23-6
U14: BateriCell_2x; battery_dock
U16: TPS61088RHLR; RHL0020A

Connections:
/HlavniDeska/3V3: C134.2, C135.2, C136.1, C137.1, C152.1, D125.1 (A), J5.4 (VDD), J7.1 (VCC), J11.36, R9.1, R10.1, R16.1, R17.1, R35.1, R36.1, R37.1, R38.1, R39.1, R41.1, R45.2, R48.2, R50.2, R51.1, U10.4 (Vout), U10.5 (SNS), U11.2 (3V3)
/HlavniDeska/5V-OUT: J11.1, J11.2, J11.3, J11.4, J11.5, J11.6, J11.7, J11.8, J11.9, J11.10, J11.11, J11.12, J11.13, TP10.1, U15.5 (D)
/HlavniDeska/ESP32S3/BOOT: C132.1, J7.4 (BOOT), R9.2, SW4.2, U11.27 (IO00-PU)
/HlavniDeska/ESP32S3/EN: C133.1, J7.3 (EN), R10.2, SW5.2, U11.3 (EN)
/HlavniDeska/ESP32S3/IO01: J1.1, U11.39 (IO01)
/HlavniDeska/ESP32S3/IO02: J1.3, U11.38 (IO02)
/HlavniDeska/ESP32S3/IO03-PD: J5.2 (DAT3/CD), R8.1, U11.15 (IO03-PD)
/HlavniDeska/ESP32S3/IO07: R29.2, U5.1 (IO1), U5.10 (NC), U11.7 (IO07)
/HlavniDeska/ESP32S3/IO08: R30.2, U5.2 (IO2), U5.9 (NC), U11.12 (IO08)
/HlavniDeska/ESP32S3/IO09: R49.2, U5.5 (IO4), U5.6 (NC), U11.17 (IO09)
/HlavniDeska/ESP32S3/IO10: R13.2, R28.2, U11.18 (IO10)
/HlavniDeska/ESP32S3/IO11: J5.3 (CMD), R41.2, U11.19 (IO11)
/HlavniDeska/ESP32S3/IO12: J5.5 (CLK), R36.2, U11.20 (IO12)
/HlavniDeska/ESP32S3/IO13: J5.7 (DAT0), R35.2, U11.21 (IO13)
/HlavniDeska/ESP32S3/IO14: J1.5, U11.22 (IO14)
/HlavniDeska/ESP32S3/IO15: R14.1, U11.8 (IO15)
/HlavniDeska/ESP32S3/IO16: R15.1, U11.9 (IO16)
/HlavniDeska/ESP32S3/IO17: J1.7, U11.10 (IO17)
/HlavniDeska/ESP32S3/IO18: J1.9, U11.11 (IO18)
/HlavniDeska/ESP32S3/IO21: R52.2, U11.23 (IO21)
/HlavniDeska/ESP32S3/IO35: Q28.1 (G), R79.1, SW3.2, U11.28 (IO35)
/HlavniDeska/ESP32S3/IO36: R16.2, SW1.2, U11.29 (IO36)
/HlavniDeska/ESP32S3/IO37: R17.2, SW2.2, U11.30 (IO37)
/HlavniDeska/ESP32S3/IO38: R11.2, R12.1, U11.31 (IO38)
/HlavniDeska/ESP32S3/IO39: R5.2, U11.32 (IO39)
/HlavniDeska/ESP32S3/IO41: J1.11, U11.34 (IO41)
/HlavniDeska/ESP32S3/IO42: J1.13, U11.35 (IO42)
/HlavniDeska/ESP32S3/IO45-PD: D122.2 (K), Q2.1 (G), R7.1, U11.26 (IO45-PD)
/HlavniDeska/ESP32S3/IO46-PD: D122.1 (K), Q1.1 (G), R6.1, U11.16 (IO46-PD)
/HlavniDeska/ESP32S3/IO47: J1.15, U11.24 (IO47)
/HlavniDeska/ESP32S3/IO48: J1.17, U11.25 (IO48)
/HlavniDeska/ESP32S3/RX_ESP: J7.5 (RX), U11.36 (IO44-RX)
/HlavniDeska/ESP32S3/TX_ESP: J7.6 (TX), U11.37 (IO43-TX)
/HlavniDeska/ESP.D+: U2.2 (Dp2), U11.14 (IO20-D+)
/HlavniDeska/ESP.D-: U2.6 (Dn2), U11.13 (IO19-D-)
/HlavniDeska/INT: J11.38, R38.2, U3.7 (INT), U11.4 (IO04)
/HlavniDeska/IO40: J11.27, U11.33 (IO40)
/HlavniDeska/ModulovyKonektor/5V: J4.2, J4.6, TP11.1, U5.4 (IO3), U9.5 (D)
/HlavniDeska/Nabijecka.D+: U2.1 (Dp1), U3.2 (D+)
/HlavniDeska/Nabijecka.D-: U2.7 (Dn1), U3.3 (D-)
/HlavniDeska/SCL: J11.40, R37.2, U3.5 (SCL), U11.5 (IO05)
/HlavniDeska/SDA: J11.39, R39.2, U3.6 (SDA), U11.6 (IO06)
/HlavniDeska/SpravceNapajeni/5V-IN: C149.1, C153.1, C154.1, C156.1, R1.1, R32.1, R57.1, TP9.1, U9.1 (S), U9.2 (S), U9.3 (S), U15.1 (S), U15.2 (S), U15.3 (S), U16.14 (VOUT), U16.15 (VOUT), U16.16 (VOUT)
/HlavniDeska/SpravceNapajeni/CHARGER_STAT: R13.1, U3.4 (STAT)
/HlavniDeska/SpravceNapajeni/Charging/BATT: C159.1, R26.1, R40.1, SW3.1, U3.13 (BAT), U3.14 (BAT), U7.1 (S), U7.2 (S), U7.3 (S), U8.1 (S), U8.2 (S), U8.3 (S)
/HlavniDeska/SpravceNapajeni/Charging/CE: Q9.3 (D), R53.2, U3.9 (~CE)
/HlavniDeska/SpravceNapajeni/Charging/SW: C6.1, L6.1, U3.19 (SW), U3.20 (SW)
/HlavniDeska/SpravceNapajeni/Charging/SYS: C160.1, C161.1, L6.2, U3.15 (SYS), U3.16 (SYS)
/HlavniDeska/SpravceNapajeni/Power multiplier/EN-5V: D122.3 (A), R47.2, TP8.1, U16.2 (EN)
/HlavniDeska/SpravceNapajeni/Power multiplier/VCC: C142.1, C143.1, C145.1, C146.1, L5.1, U8.5 (D), U10.1 (EN), U10.6 (Vin), U16.9 (VIN)
/HlavniDeska/SpravceNapajeni/USB_SEL: R2.2, U2.10 (SEL), U3.24 (DSEL)
/HlavniDeska/USB/D+: J2.A6 (D+), J2.B6 (D+), U2.3 (Dp), U13.4 (IO3)
/HlavniDeska/USB/D-: J2.A7 (D-), J2.B7 (D-), U2.5 (Dn), U13.2 (IO2)
/HlavniDeska/USB/USB_CC1: J2.A5 (CC1), R4.1
/HlavniDeska/USB/USB_CC2: J2.B5 (CC2), R3.1
/HlavniDeska/USB/V_USB: C5.1, C162.1, J2.A4 (VBUS), J2.A9 (VBUS), J2.B4 (VBUS), J2.B9 (VBUS), R2.1, R53.1, TP1.1, U2.9 (VCC), U3.1 (VBUS), U13.1 (IO1), U13.5 (IO4)
GND: C5.2, C7.2, C132.2, C133.2, C134.1, C135.1, C136.2, C137.2, C142.2, C143.2, C144.2, C145.2, C146.2, C147.2, C149.2, C150.2, C151.2, C152.2, C153.2, C154.2, C155.2, C156.2, C157.2, C158.2, C159.2, C160.2, C161.2, C162.2, J1.2, J1.4, J1.6, J1.8, J1.10, J1.12, J1.14, J1.16, J1.18, J2.A1 (GND), J2.A12 (GND), J2.B1 (GND), J2.B12 (GND), J2.S1 (SHIELD), J4.3, J4.5, J5.6 (VSS), J5.9 (SHIELD), J7.2 (GND), J11.14, J11.15, J11.16, J11.17, J11.18, J11.19, J11.20, J11.21, J11.22, J11.23, J11.24, J11.25, J11.26, J11.37, Q1.2 (S), Q2.2 (S), Q7.2 (S), Q8.2 (S), Q9.2 (S), Q28.2 (S), R3.2, R4.2, R6.2, R7.2, R8.2, R12.2, R19.2, R21.1, R34.1, R47.1, R55.2, R58.1, R79.2, SW1.1, SW2.1, SW4.1, SW5.1, U2.4 (GND), U2.8 (OEb), U3.8 (OTG), U3.17 (PGND), U3.18 (PGND), U3.25 (PGND), U5.3 (G), U5.8 (G), U7.4 (G), U10.2 (GND), U10.7 (GND), U11.1 (GND), U11.40 (GND), U11.41 (GND), U12.6 (GND), U13.3 (G), U13.8 (G), U14.2 (-), U14.4 (-), U16.0 (PGND), U16.20 (AGND), U16.21 (PGND)
unnamed: BZ1.2 (+), R15.2
unnamed: BZ1.1 (-), R14.2
unnamed: C157.1, R56.2
unnamed: D125.4 (BK), R28.1
unnamed: D125.3 (GK), R5.1
unnamed: D125.2 (RK), R11.1
unnamed: F1.2, U14.3 (+)
unnamed: F2.2, U14.1 (+)
unnamed: J4.1, R29.1, R48.1
unnamed: J4.4, R30.1
unnamed: J4.7, R45.1, R49.1
unnamed: Q1.3 (D), R1.2, U9.4 (G)
unnamed: Q2.3 (D), R32.2, U15.4 (G)
unnamed: Q4.3 (D), Q5.1 (G), U12.1 (OD)
unnamed: Q4.1 (G), Q4.2 (S), Q6.1 (G), Q7.1 (G), Q8.3 (D), R51.2, R52.1
unnamed: Q5.3 (D), Q6.3 (D), R40.2, U8.4 (G)
unnamed: Q6.2 (S), Q7.3 (D), Q8.1 (G), R50.1
unnamed: Q9.1 (G), U12.3 (OC)
unnamed: Q5.2 (S), Q28.3 (D)
unnamed: C6.2, U3.21 (BTST)
unnamed: R19.1, U3.10 (ILIM)
unnamed: C147.1, C151.1, U3.23 (PMID)
unnamed: C7.1, R20.1, U3.22 (REGN)
unnamed: R20.2, R21.2, U3.11 (TS)
unnamed: F1.1, F2.1, U7.5 (D)
unnamed: C144.1, R26.2, U12.5 (VCC)
unnamed: R34.2, U12.2 (VM)
unnamed: C148.2, U16.8 (BOOT)
unnamed: C158.1, R56.1, U16.18 (COMP)
unnamed: R57.2, R58.2, U16.17 (FB)
unnamed: R54.2, U16.3 (FSW)
unnamed: R55.1, U16.19 (ILIM)
unnamed: C150.1, U16.10 (SS)
unnamed: C155.1, U16.1 (VCC)
SW: C148.1, L5.2, R54.1, U16.4 (SW), U16.5 (SW), U16.6 (SW), U16.7 (SW)
